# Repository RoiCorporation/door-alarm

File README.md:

# Door alarm PCB design
Repository with the PCB design for the door alarm project.

## 📋 Schematic

## 📐 Finished design

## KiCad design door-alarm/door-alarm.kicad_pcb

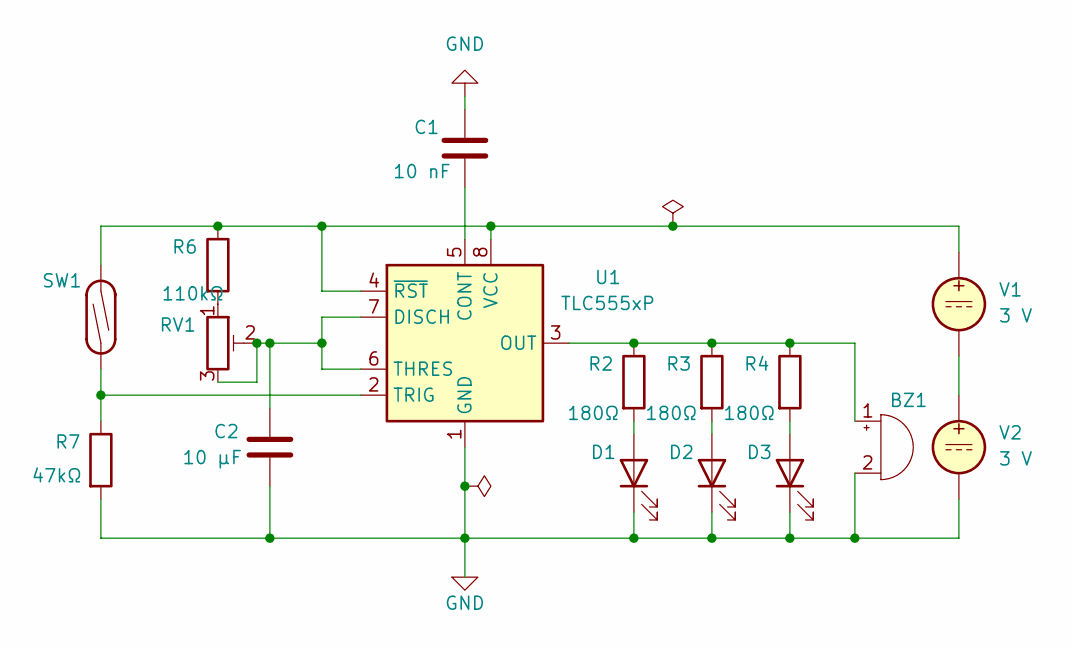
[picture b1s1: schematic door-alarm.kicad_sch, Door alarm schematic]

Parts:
BZ1: Buzzer; Buzzer_TDK_PS1240P02BT_D12.2mm_H6.5mm
C1: 10 nF; C_Disc_D5.0mm_W2.5mm_P5.00mm
C2: 10 µF; C_Disc_D5.0mm_W2.5mm_P5.00mm
D1, D2, D3: LED; LED_D5.0mm
R2, R3, R4: 180Ω; R_1206_3216Metric
R6: 110kΩ; R_1206_3216Metric
R7: 47kΩ; R_1206_3216Metric
RV1: R_Potentiometer_Trim; Potentiometer_Bourns_3266Z_Horizontal
SW1: SW_Reed; SW_SPDT_REED_MSDM-DT
U1: TLC555xP; DIP-8_W7.62mm
V1, V2: 3 V; BatteryHolder_Keystone_3002_1x2032

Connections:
GND: BZ1.2 (-), C1.1, C2.2, D1.1 (K), D2.1 (K), D3.1 (K), R7.2, U1.1 (GND), V2.2
unnamed: BZ1.1 (+), R2.1, R3.1, R4.1, U1.3 (OUT)
unnamed: D1.2 (A), R2.2
unnamed: D2.2 (A), R3.2
unnamed: D3.2 (A), R4.2
unnamed: R6.2, RV1.1
unnamed: C1.2, U1.5 (CONT)
unnamed: C2.1, RV1.2, RV1.3, U1.6 (THRES), U1.7 (DISCH)
unnamed: R7.1, SW1.1, U1.2 (TRIG)
unnamed: R6.1, SW1.2, U1.4 (~RST), U1.8 (VCC), V1.1
unnamed: V1.2, V2.1

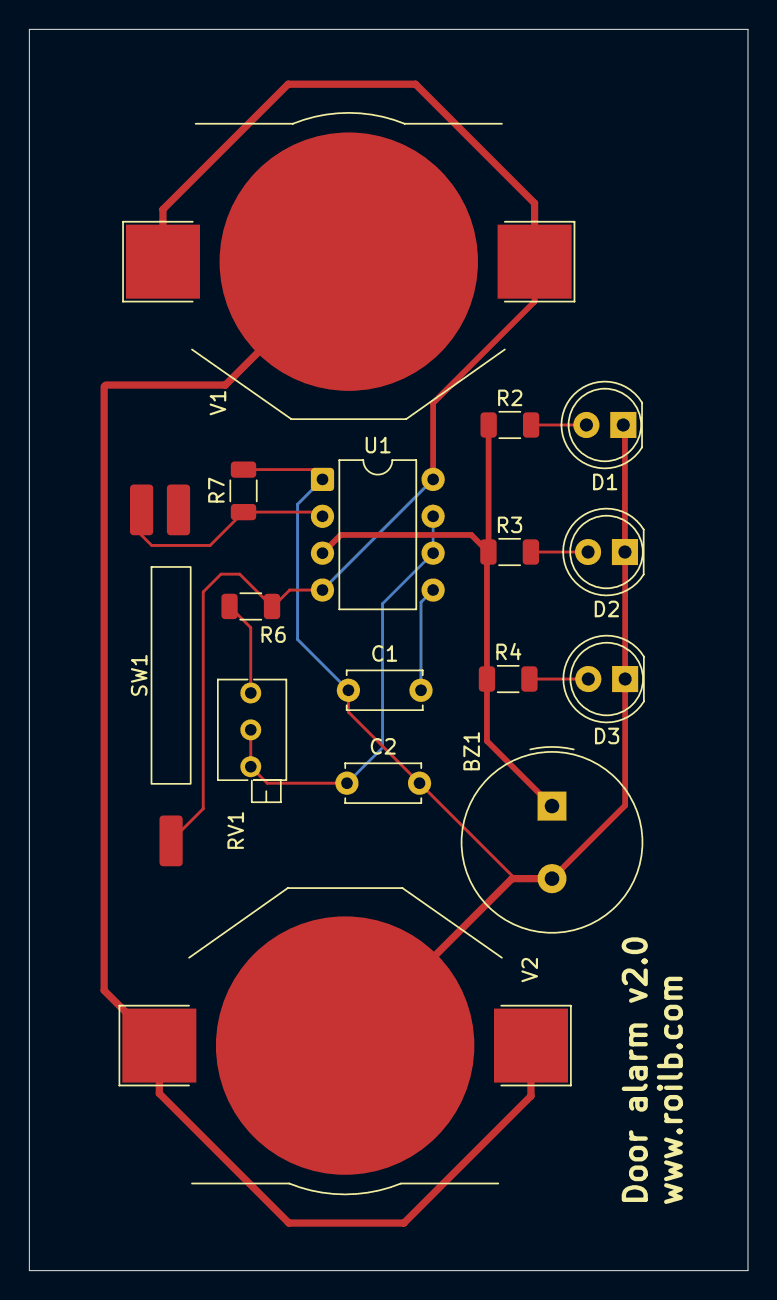
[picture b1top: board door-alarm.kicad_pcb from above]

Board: 2 copper layers, 49.5 x 85.5 mm, 16 parts (0 on the bottom side), 11 nets.

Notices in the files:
README.md:
License: MIT
